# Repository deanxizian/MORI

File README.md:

# MORI：正式机器人与可行性验证小车

本仓库包含两个独立维护和编号的项目。各项目的版本、模型、硬件、软件与验证状态见对应入口；两者的实测结果不互相继承。

| 项目 | 用途 | 入口 |
|---|---|---|
| 正式机器人 | WeAct STM32F412 主控、四执行器机器人 | **[robot/](robot/README.md)** |
| 可行性验证小车 | 树莓派 4B 两轮平衡与模块验证 | **[test_rig/](test_rig/README.md)** |

## 目录结构

```text
MORI/
├── robot/          正式机器人：尺寸、合同、机械、PCB、固件、应用、文档与工具
├── test_rig/       验证小车：结构、模块、控制源码、关键实测记录
├── projects.json   两个项目的入口与版本清单位置
├── tools/          仓库级完整性检查
└── .github/        两项目独立检查工作流
```

## 资料入口

- [版本与目录规则](VERSIONING.md)
- 正式机器人：[当前需求](robot/docs/REQUIREMENTS.md) · [当前状态](robot/docs/CURRENT_STATUS.md) · [资料索引](robot/docs/PROJECT_INDEX.md)
- 验证小车：[装配说明](test_rig/ASSEMBLY.md) · [当前状态](test_rig/STATUS.md) · [控制源码](test_rig/control/README.md)
- [正式机器人下载与重建](robot/docs/GITHUB_ARCHIVE.md)

## 离线检查

Python 3.12+ 离线检查，不连接硬件：

```sh
python3 tools/check_workspace.py --allow-lfs-pointers
python3 robot/tools/check_project.py --allow-lfs-pointers
python3 test_rig/tools/check_release.py
```

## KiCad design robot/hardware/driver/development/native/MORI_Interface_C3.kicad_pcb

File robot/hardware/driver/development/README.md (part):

# C3 收尾开发工作区

当前本地开发入口为 **C3 R188C / 19 项未连接**。R188 已修复 U1702 比较器输入的局部参考地缺口，并缩短 C1002 的直接回地路径；没有再消除未连接项。原 40 项中的剩余比例仍为 47.5%，不代表工程或时间完成率。

最新 [R190 研究](evidence/R190_study/README.md)已归档，A/B/C 均未采用。B 为 19 未连接 / 0 其他 DRC，但完整接收检查未完成；C 接通 RAW 后损坏原供电和热连接，已拒绝。入口与 77 个非 PCB 源成员保持。用户已允许评估 70×40 mm 的机械空间，安装孔和接口保持；独立机械检查尚未完成，也没有采用扩板。

[R188C 接收说明](evidence/R188C/README.md) · [R188 三稿比较](evidence/R188_study/README.md) · [当前参考地待审队列](evidence/R188C/reference-review-queue.json) · [R182 空间比较](evidence/R182_study/README.md) · [继续开发](NEXT.md)

此前 [R189 四稿比较](evidence/R189_study/README.md)均未采用。R1304 在保留相邻走线的 12 个几何姿态中未找到两端完整访问；这是限定搜索，不是整板不可布通的证明。A–C 割裂 CAM 供电，A 还孤立一处地焊盘；D 恢复全部原连接和 50 项供电检查，但 J401 正面接地热焊盘仍有一条引线接入死铜，原生 DRC 不通过。下一步把 R402、相邻 WHEEL_BUS 出线、R1304 输入和 OV 换层一起重排，并保留真实供电及接地热连接。当前板框、R188C 原生文件及 77 个非 PCB 成员均保持，参考地待审队列仍为 75 段／36 网。

R188C 的 19 未连接 / 0 其他 DRC / 0 图板差异 / 0 启用 ERC、2524 项精确修改检查、50 供电铜宽、155 地焊盘单组、63 关键邻接及新旧参考地回归通过。一只地孔与一只采样孔按明确计划移动，10 段换成 13 段；C1002 的 0.20 mm 宽直接回地从 4.043503 mm 缩短至 2.568503 mm。没有移动器件、增加孔或更改板框／规则。当前 1418 段 / 324 孔 / 215 器件；114 地孔身份保留，其中 113 个位置不变，全部仍接触两参考层的实际地填铜。77 个非 PCB 成员原字节保持，十张源板／最终局部图已实际查看。

完整参考地扫描覆盖 1305 段非 GND 走线，待审项从 R187F 的 76 段／37 网降至 **75 段／36 网**；U1702 INA+ 原约 0.318712 mm² 缺口消除，未新增或恶化保留走线的缺口。这些是几何筛查提示，不是原生 DRC 或已证实电气故障。采样线对相邻 In2 接收端电源面新增约 0.001729 mm² 未屏蔽投影，按更近的连续 In4 地、原层叠与缩短的回地逐项审查，仅接受为开发布局。最近两处过孔名义铜间距约 0.204／0.208 mm，满足原规则，但没有推定额外加工裕量。六项历史换层提示、完整噪声／热／瞬态和实物资格仍未完成。

供电规划保护已按 R188C 重新计算，50 项原连接／铜宽及 50 项序列化读回检查通过，供下一轮使用。完整参考地扫描沿用 `scripts/audit_reference_coverage.py`，原阈值／自身换层豁免规则保持。[R187F](evidence/R187F/README.md)已消除的 IMU 时钟四处和 WHEEL_TX 一处缺口保持；其扫描器与冻结源板 1296 段逐段核对的历史证据不改写。

此前 R186 四稿均未采用。分压／滤波四件换位能放下局部支路，但完整端点未恢复；D 接回两条诊断路线后损失 7 项供电检查，GND 分成 153+2，已拒绝。局部拥挤明确，仍未证明整板必须扩大。[R186 源板扫描](evidence/R186_study/README.md)的 81 段／38 网属于 R181C 历史结果，当前以 R188C 队列为准。

此前 R185 也未采用 PCB 修改。独立 I 缩短 C601 回地并补回 3.3 V，2508 项数字核对通过、历史换层提示降到 5 项，但 TVS／相邻层控制线的耦合审查未关闭；J 的绕行又产生新参考地缺口。原地孔位置一律冻结是早期工具限制，已更正为明确计划下的地孔移动及直接回地校验；R186 又补齐真实焊盘内部偏移出口的六项正反例。原生规则和验收要求保持。

地孔参考连接检查也已改用实际填铜，排除自身铜环造成的假阳性；五项正反例及 I 的 2508 项重跑通过，当前板与候选的既有计数均未改变，旧证据保留。

此前 R184 未采用任何修改。扩大到门极 RC 后，充电泵电容的移位仍受原 UPS 5 V 供电桥限制；独立释放桥线才出现新的几何组合。原生 D 虽能放下器件，仍为 26 未连接 / 3 悬空过孔，供电只过 46/50，未接收；下一步须把实际换层孔与完整供电恢复纳入同一布局。有限搜索不证明整板不可布通。[R182](evidence/R182_study/README.md)已准备 **70×40 mm 独立空间候选**及静态比较：只沿原生 +Y 加 5 mm，孔/接口不动；候选尚未布通、没有新增区域参考地或机械适配，不能制造。用户已允许评估其机械空间；评估尚未完成，尚未采用。当前板仍为 70×35 mm / R188C / 19 项未连接。

[此前 R181 比较](evidence/R181_study/README.md)保留 A–H，仅接收 C 的采样支路。其余联合移动、供电冲突或参考地失败方案均未采用；R182 按新源重新生成供电保护，没有沿用旧源检查冒充通过。

R181C 曾将采样支路从 25.512702 mm 缩短到 18.203088 mm，改走 F.Cu 并复用两处原换层孔，退休一个无剩余连接的非地孔。该阶段 2523 项精确差异及电气回归通过，为 1409 段 / 324 孔 / 215 器件，八张局部/源板图已查看。该支路距 Q1602 漏极焊盘最小名义铜间距 0.2225 mm，距 C707.1 为 0.375 mm；这些数值和 DRC 不能证明采样噪声、瞬态或热性能合格。源证据完整保留。

本目录是从 `main aa94ddd` / C3 R108P 原包恢复的**独立开发候选**，尚未采用到当前发布，也没有制造或实物资格。正式已发布入口仍为上级 R108P。

任务：完成接口板剩余连线及规范审查。保留 70 × 35 × 1.6 mm 六层板、四安装孔、68 核心针位、九连接器、既定电路和保护策略。优先向器件外侧出线，比较朝向/位置，避免多余绕折；电源/去耦关键环路优先。确有必要的例外须逐项说明。

验收包含：

1. 原生填铜后的全严重级 DRC、未连接、图板一致性和 ERC；明确历史忽略项，不降低规则。
2. 全部旧连接组、供电铜宽、GND、Kelvin 取样、关键器件邻接和敏感区回归。
3. 连续参考地及历史换参考层提示（原七项，R129D 后剩六项）；新增孔不可割裂供电，也不可破坏旧信号参考地。
4. 全板逐线/逐孔与各层静态视觉审查；自动几何筛查不代替实际看图。
5. 电源/保护/连接器额定及完整 BOM、接口针表、机械交接、线束和采购成本。缺实测/厂家数据须明确保留，不能凭连通或 DRC 放行。
6. 可复查的原生工程、来源和修改清单、实际命令与输出、复现脚本；通过 PR 发布，合并须针对该 PR 授权。

不运行设备、不烧录、不下单、不在未布完时导出制造文件。旧发布 ZIP、原始厂家资料和冻结证据不被覆盖。物理热/浪涌/EMC/动态性能保持 NOT_TESTED，直到有相应实测证据。

## 发布快照与复现

[本次发布审查与原生复查](evidence/publication_20261029/README.md)保留固定接口、原连接、归档完整性、离线测试及明确未完成项。

本次 PR 以一个汇总提交发布当前入口与冻结研究资料。历史记录中的中间提交号只标识本地来源，不要求这些提交出现在远端历史中。复现以文件哈希为准：当前 `native/` 的 77 个非 PCB 成员与 R108P 原包保持原字节，旧版源 PCB 在各接收/研究目录中保留；恢复对应源 PCB、计划和依赖后，在独立目录运行开发脚本。历史命令及冻结脚本中的本机路径、源 HEAD 断言记录当时环境，不能把它们当成新机器可直接运行的配置，也不要改写冻结记录以制造一致。

## 本机复现环境

KiCad 10.0.7；其自带 Python 3.9.13 用于原生 `pcbnew`，独立环境在 `robot/.state/c3-completion/venv`，几何计算用 Shapely 2.0.7。仓库完整性脚本另用 Python 3.12+。`.state` 中的基线由上级 ZIP 解出，78 个成员均按 manifest 验证。

本机原生基线复查：40 项未连接，其他 DRC 0，图板差异 0；启用项全严重级 ERC 0。没有据此提高工程资格。

## 已保留的 R178L 接收记录

以下为对应修订的历史记录；当前入口以本文开头和 STATUS.json 为准。

2026-10-29，D302 改为正面 `(2,23)` / 270°，保留原型号、极性及原生禁布区，以两条短线接到已有 CLR/FAULT 过孔。当前 **19 项未连接，0 其他 DRC / 图板差异 / 启用 ERC**；剩余数量比例 **47.5%**，不是工程或时间完成率。

2515 项精确修改核对、全部原连接、50 铜宽、155 地焊盘、63 邻接及新旧参考地通过；114 原地孔、全部其他原孔、固定接口和 77 个非 PCB 成员保持。九张局部图已查看，新 FAULT 避开对侧 DVDT 铜及电感本体投影；全板、厂家完整布局及实物资格仍未完成。正式发布仍为 R108P，不可制造。

[当前接收记录](evidence/R178L/README.md) · [原生结果](evidence/R178L/result.json) · [精确核对](evidence/R178L/planned-delta.json) · [剩余连接](evidence/R178L/remaining_connections.csv) · [对比研究](evidence/R178_study/README.md) · [继续开发](NEXT.md)

## 前一已采用开发稿：C3 R168G

2026-10-28，Q1701 的 FAULT 支路已接入主组，现为 **20 项未连接，0 其他 DRC / 图板差异 / 启用 ERC**。FAULT 尚余 U1701.5、D302.1 两个孤立端。**20/40 = 50% 仅为剩余未连接数量比例**，不是工程或时间完成率。

联合调整 Q1701、U1702、C1702 和三只原非地过孔，完整恢复原引线，新增一只 FAULT 孔及 21.090180 mm In2 主干。2566 项明确差异、全部旧连接、50 铜宽、155 地焊盘、63 邻接及新旧参考地通过；114 原地孔、原 0.48 mm 供电通道、固定接口和 77 个非 PCB 源成员保留。现为 1398 段 / 325 孔 / 215 器件。

十二张局部六层图已实际检查，无新同面名义本体穿越。对侧/内层投影和四处跨层交叉已记录边界；完整输入噪声、去耦环路、保护动态、热/耦合与实物仍未资格化。正式已发布入口仍为 R108P，不可制造。

[接收说明](evidence/R168G/README.md) · [检查结果](evidence/R168G/result.json) · [精确差异](evidence/R168G/planned-delta.json) · [局部审查](evidence/R168G/visual_review.json) · [剩余连接](evidence/R168G/remaining_connections.csv) · [未采用研究](evidence/R168_study/README.md)

后续 [R169 研究](evidence/R169_study/README.md)比较 INA300 原朝向与 180° 朝向，并联合调整 R1310。E 接通 FAULT 支路，却割裂 3.3 V，且原取样、LIMIT 与显式回地未恢复，未采用。原生入口及 **20 项 / 50%** 不变；具体下一步见 [继续开发](NEXT.md)。

[R170 研究](evidence/R170_study/README.md)继续比较原出口与四只无源器件成组调整，保留十块原生稿。J 已恢复 IN− 短线及部分原供电，但 3.3 V 孔／引线禁布冲突、旧连接和 RLIMIT 显式回地仍未完成，未采用；当前入口与 **20 项 / 50%** 不变。

[R171 研究](evidence/R171_study/README.md)显式核对旧 VS 孔的孤立内层铜区，并在 E 恢复 VS 与 ENABLE。E 为 27 项未连接、5 项悬空，旧连接及 RLIMIT 显式回地仍未完成，未采用。已采用 R168G 与 **20 项 / 50%** 保持；原生失败、工具正反例及五张局部图均保留。

[R172 空间检查](evidence/R172_study/README.md)确认 INA300 附近局部拥挤，但尚未证明整板面积不足。依赖筛查指出需扩大到 U1302 等相关器件联合排布；未构建新板，入口与 **20 项 / 50%** 不变。具体空间限制须及时报告，板框或已确认结构变化先以模型和静态对比确认。

[R173 联合布局研究](evidence/R173_study/README.md)构建四块比较稿；E 有显式 RLIMIT 回地，但五项实际 3 mm 邻接要求、原供电／连接和一处新参考地缺失仍失败，全部未采用。下一步联合安排两颗 IC 和全部六只外围；当前入口及 **20 项 / 50%** 不变。

[R174 完整布局与供电对照](evidence/R174_study/README.md)的六块原生稿均满足 63 项邻接要求，但仍未采用。D 有显式 RLIMIT／去耦回地；单项撤销对照分别确认新 IN− 孔削弱 UPS 0.48 mm 通道、In3 回地割裂 3.3 V 宽铜通道。局部空间瓶颈已报告，尚未证明必须扩板；原连接和供电须一起恢复。采用入口及 **20 项 / 50%** 不变。

[R175 供电保护与端口研究](evidence/R175_study/README.md)保留九块原生候选。A 恢复上述 UPS／3.3 V 宽铜回归；G 通过监控器／电容旋转恢复 155 个地焊盘单组并构建较短的显式回地。A／G 均为 31 opens / 7 dangling / 0 parity / 0 enabled ERC，原连接与供电支路仍未恢复，全部未采用。正输入、CT 及其他支路继续成组布局／出线检查，扩大板框的必要性仍未证明；当前入口及 **20 项 / 50%** 不变。

[R176 原针位与供电研究](evidence/R176_study/README.md)保留 11 块原生候选。H 恢复两路输入、LIMIT 和 155 地焊盘单组，但 25.593 mm 新回地割裂了 3.3 V 分配；后续短接和 In2 修复也出现其他供电或参考地退化，全部未采用。已记录 C1601／INA300 周边的明确装配包络冲突；局部拥挤有证据，必须扩板尚未证明。禁布分区工具修复通过 18 项检查及四次原生重读，原生规则未放宽。当前入口仍为 **R168G / 20 项 / 50% 连通数量比例**。

[R177 供电保护与 D302 比较](evidence/R177_study/README.md)建立了覆盖全部 50 项原供电检查、读回验证通过的规划保护，并保存 11 块原生稿。G 达到 19 / 0 / 0 / 0，但新增 CLR 的 L701／SW 投影审查尚未闭合；K 避开 L701，却违反 J102.2 的四条热连接要求。两稿均未采用，当前仍 **20 项 / 50%**。局部空间限制有证据，尚未证明必须扩板；不能把候选连通或数字检查通过写成工程完成。

## 先前接收：C3 R165M

以下是当时的接收与后续研究记录；当前入口以上方 R168G 为准。

2026-10-28，原生开发入口为 **R165M，21 项未连接，0 其他 DRC / 图板差异 / 启用 ERC**。U1301 的 OV 网络由两组接成一组；联合布局中涉及的原 UV、FAULT 和 ENABLE 偏置连接全部恢复。原理图、值、针表、固定接口和规则保持。

17 个器件成组调整，其中两只电阻换面；以显式计划替换旧铜和非地换层孔，全部 114 个原地孔保留。原 OV 孔移至 `(55.9,33.9)`，FAULT 接入孔位于 `(54.3,33.9)`，让两条输出信号通过既有 3.3 V 孔之间的有参考地通道。现为 1366 段 / 324 孔 / 215 器件。

2807 项计划差异、全部旧连接、50 项铜宽、155 地焊盘、63 邻接及新旧参考地检查通过。十二张原生几何图已实际审查，新同面名义本体穿越为 0；16 组对侧/内层器件投影明确记录参考地、耦合和热检查边界。77 个非 PCB 工程成员保持原字节。

**21/40 = 52.5% 仅为剩余未连接数量比例。** 六项历史回流提示、整板风格、完整厂家布局、热/耦合和实物资格未完成；正式发布仍 R108P，机械与软件未采用，不可制造。

[接收说明](evidence/R165M/README.md) · [当前结果](STATUS.json) · [剩余连接](evidence/R165M/remaining_connections.csv) · [图审](evidence/R165M/visual_review.json) · [R165 研究](evidence/R165_study/README.md) · [继续开发](NEXT.md)

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
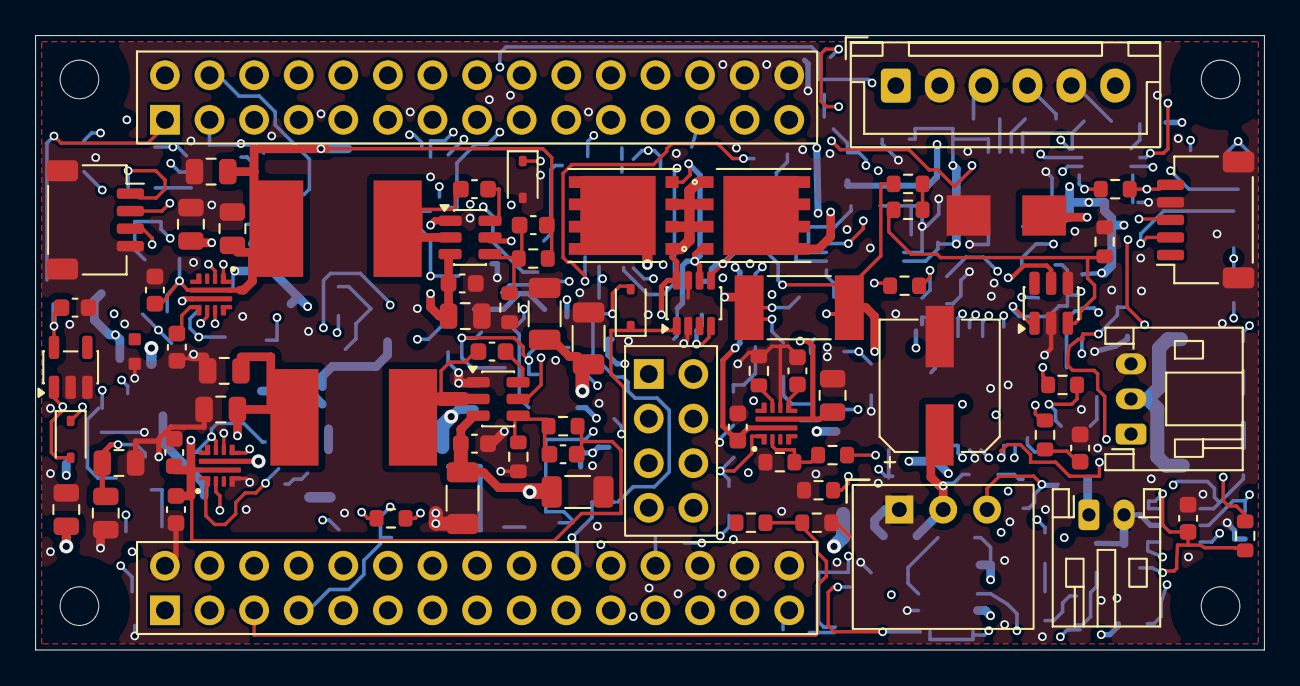
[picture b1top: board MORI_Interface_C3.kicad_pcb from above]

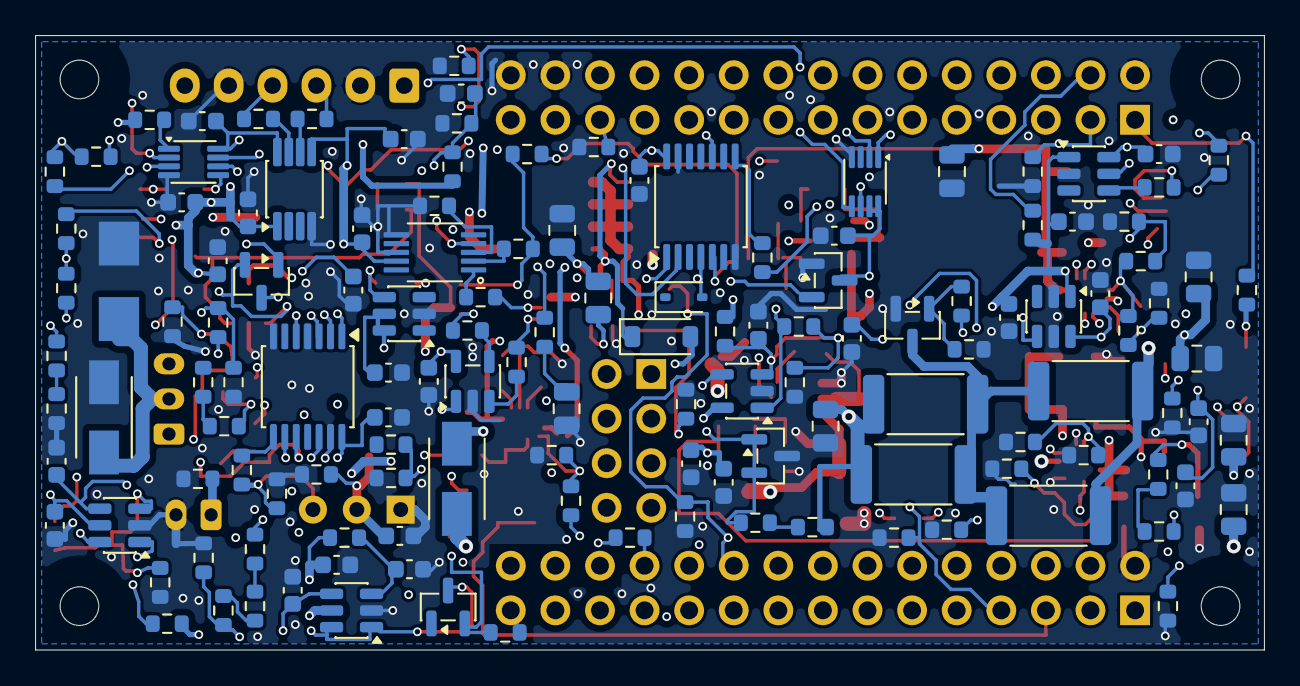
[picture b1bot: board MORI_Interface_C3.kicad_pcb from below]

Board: 6 copper layers, 70.0 x 35.0 mm, 215 parts (135 on the bottom side), 106 nets.

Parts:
C301, C302, C303, C401, C402, C501, C502, C503, C504, C601, C602, C702, C706, C906, C1001, C1002, C1003, C1101, C1102, C1202, C1209, C1303, C1304, C1402, C1502, C1503, C1701, C1702: 100nF 16V X7R; C_0603_1608Metric
C505, C708, C803, C1201, C1401: 1uF 16V X7R; C_0603_1608Metric
C701, C703, C704, C705, C709, C802, C903, C904, C905, C909, C910, C911, C1205, C1206, C1207, C1208: 22uF 25V X5R; C_0805_2012Metric
C707, C907, C1301, C1302, C1403, C1501: 100pF 50V C0G; C_0603_1608Metric
C710, C801, C1203, C1204: 1nF 50V C0G; C_0603_1608Metric
C901, C908, C912, C913: 10uF 50V X7R; C_1206_3216Metric
C902: 100nF 50V X7R; C_0603_1608Metric
C1404: 220uF 16V polymer; Panasonic_SVPF_C6
C1601, C1602, C1603: 220nF 50V X7R; C_0805_2012Metric
D301, D302, D1001, D1601: BAT54WS-7-F; D_SOD-323
D901, D1803: B340LA-13-F; Diodes_SMA
D1602: BZT52C12-7-F; D_SOD-123
D1801, D1802: SMBJ13CA-13-F; Diodes_SMB
H1, H2, H3, H4: MountingHole_2.2mm_M2
J101, J102: X6521FV-2x15-C85D32; XKB_2x15_WeAct_AC_BD_ConnectedInner6L
J105: PM254-2-04-Z-8.5; HCTL_2x04_WeAct_E_ConnectedInner6L
J401: S3B-PH-K-S(LF)(SN); JST_PH_S3B-PH-K_1x03_P2.00mm_Horizontal_ConnectedInner6L
J402: HC-5264-3AW; HCTL_5264_3AW_ConnectedInner6L
J501: SM04B-SRSS-TB(LF)(SN); JST_SH_SM04B-SRSS-TB_1x04-1MP_P1.00mm_Horizontal
J502: SM05B-SRSS-TB(LF)(SN); JST_SH_SM05B-SRSS-TB_1x05-1MP_P1.00mm_Horizontal
J701: B6B-XH-A(LF)(SN); JST_XH_B6B-XH-A_1x06_P2.50mm_Vertical_ConnectedInner6L
J702: S2B-PH-K-S(LF)(SN); JST_PH_S2B-PH-K_1x02_P2.00mm_Horizontal_ConnectedInner6L
L701: 10uH MWSA0804S-100MT; L_Sunlord_MWSA0804S
L901: 10uH; L_Sunlord_MWSA0804S
Q1301, Q1401, Q1701: AO3400A; SOT-23
Q1601, Q1602: CSD17577Q5A; TI_CSD17577_Q5A
R301, R305, R403, R406, R716, R802, R804, R1207, R1704: 10k; R_0603_1608Metric
R302, R303, R304, R404, R407, R903, R1031, R1032, R1033, R1201, R1301, R1310, R1311, R1312, R1407, R1602, R1702, R1703, R1705: 100k; R_0603_1608Metric
R402, R405, R501, R502, R603, R604, R1406: 33R; R_0603_1608Metric
R505, R506, R601, R602, R1309: 4.7k; R_0603_1608Metric
R701, R1001, R1002, R1305, R1502: 54.9k 0.1%; R_0603_1608Metric
R702, R712, R714, R902, R1011, R1012, R1205, R1303, R1306, R1307, R1404, R1504: 10k 0.1%; R_0603_1608Metric
R711, R1302, R1505: 18k; R_0603_1608Metric
R713, R1202, R1203, R1503: 24.3k 0.1%; R_0603_1608Metric
R715, R1206: 1.65k; R_0603_1608Metric
R801: 27k; R_0603_1608Metric
R803: 36k; R_0603_1608Metric
R805: 3.32k; R_0603_1608Metric
R806, R1003, R1021, R1022, R1102, R1208, R1401, R1402, R1601: 1k; R_0603_1608Metric
R901, R1304, R1501: 90.9k 0.1%; R_0603_1608Metric
R1101: 20mR 1% 1W; Vishay_WSL2512_20mR
R1103, R1104, R1706, R1707: 220R; R_0603_1608Metric
R1308: 100k; R_0603_1608Metric_R1308Edge
R1403: 16.5k 0.1%; R_0603_1608Metric
R1405: 1M; R_0603_1608Metric
R1411, R1412, R1413, R1414: 10R / 2W pulse; R_2512_6332Metric
R1701: 1.74k; R_0603_1608Metric
TH1501: 10k NTC / 3435K; TDK_NTCG_1608
U301: SN74LVC1G74DCUR; VSSOP-8_2.3x2mm_P0.5mm
U302: STWD100NXWY3F; SOT-23-5
U303: TLV803EA29DBZR; SOT-23
U401: SN74LVC2G32DCUR; VSSOP-8_2.3x2mm_P0.5mm
U402: 74LVC125APW,118; TSSOP-14_4.4x5mm_P0.65mm
U501, U502: SN74LVC1T45DBVR; SOT-23-6
U601: TCA9517DGKR; VSSOP-8_3x3mm_P0.65mm
U701, U901: TPS54302DDCR; SOT-23-6
U702, U801: TPS259470LRPWR; TI_RPW0010A
U1001: TMUX1511PWR; TSSOP-14_4.4x5mm_P0.65mm
U1101: INA180A2IDBVR; SOT-23-5
U1201: TPS259474LRPWR; TI_RPW0010A
U1301, U1501, U1702: TPS3700DDCR; SOT-23-6
U1302: TPS3808G01DBVR; SOT-23-6
U1401: TLV1811DBVR; SOT-23-5
U1402: TL431BIDBZR; SOT-23
U1601: LM74502DDFR; Texas_DDF0008A_SOT-8_1.6x2.9mm_P0.65mm
U1701: INA300AIDGSR; TI_DGS0010A

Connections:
/01 / Core/ACT_CURRENT_ADC: J101.7, R1003.2, R1033.2
/01 / Core/ARMED: D1601.2, J101.20, R304.1, R903.2, R1201.2, U301.3, U901.5, U1201.1, U1302.3
/01 / Core/ARM_CLK: J102.3, R302.1, U301.1
/01 / Core/BAT_ADC: J101.5, R1021.2, R1031.1
/01 / Core/HEAD_OE_REQ_N: J102.6, R406.2, U401.5
/01 / Core/HEAD_RX: J101.14, U402.11
/01 / Core/HEAD_TX: J101.11, U402.9
/01 / Core/IMU_SCL: J102.17, J502.3, R506.2
/01 / Core/IMU_SDA: J102.20, J502.2, R505.2
/01 / Core/LINK_RX: J102.22, U502.3
/01 / Core/LINK_TX: J102.21, U501.3
/01 / Core/MOTION_5V: C802.1, J102.27, J102.29, U801.6
/01 / Core/NRST: D301.1, J105.7
/01 / Core/UPS_SCL_MCU: J101.24, R601.2, U601.2
/01 / Core/UPS_SDA_MCU: J102.1, R602.2, U601.3
/01 / Core/WDI: J102.25, R303.1, U302.4
/01 / Core/WHEEL_ADC: J101.8, R1022.2, R1032.2
/01 / Core/WHEEL_OE_REQ_N: J102.5, R403.2, U401.1
/01 / Core/WHEEL_RX: J102.15, U402.6
/01 / Core/WHEEL_TX: J102.18, U402.2
/03 / Motor_Buses/DISARMED: U301.5, U401.2, U401.6
/03 / Motor_Buses/HEAD_BUS: J402.3, R405.2, R407.1, U402.12
/03 / Motor_Buses/WHEEL_BUS: J401.1, R402.2, R404.1, U402.5
/06 / CAM_Buck/CAM_REG_3V87: C703.1, C704.1, C705.1, C707.1, C708.1, L701.2, R701.2, R711.2, R713.2, U702.5
/06 / CAM_Buck/UPS_5V: C701.1, C702.1, C803.1, J701.1, R801.2, R803.2, R806.2, U701.3, U701.5, U801.5
/07 / CAM_Protection_Start/CAM_BAT_OUT: C709.1, J702.1, R716.2, U702.6
/09 / Head_Buck/HEAD_BUCK_IN: C901.1, C902.1, C908.1, C912.1, C913.1, D901.1, U901.3
/13 / Head_Fault_Delay/HEAD_UV_N: Q1301.2, R1308.1, U1301.1
/14 / Head_Regen/HEAD_REF_2V495: R1402.1, U1401.4, U1402.1, U1402.2
/14 / Head_Regen/H_DUMP_SENSE: C1403.1, R1403.1, R1404.2, R1405.1, U1401.3
/15 / Head_Output_OV/H_DUMP_TEMP: C1503.1, R1505.1, TH1501.1, U1501.3
/16 / Actuator_Direct_Switch/ACT_FET_SOURCE: D1602.2, Q1601.1, Q1601.2, Q1601.3, Q1602.1, Q1602.2, Q1602.3, U1601.8
/16 / Actuator_Direct_Switch/ACT_GATE: D1602.1, Q1601.4, Q1602.4, R1601.1, U1601.6
/17 / Actuator_Overcurrent/ACT_UV_N: Q1701.2, R1705.1, U1702.1
/ACT_BAT_SWITCHED: Q1602.5, Q1602.6, Q1602.7, Q1602.8, R1101.1, R1103.1, R1706.1
/ACT_CURRENT_FILTERED: C1102.1, R1102.2, U1001.9
/CLR_N: D301.2, D302.2, J102.4, R301.1, U301.6, U302.1, U303.2, U1001.1, U1001.4, U1001.10
/FAULT_N: D302.1, J102.7, Q1301.3, Q1701.3, R305.2, U1301.6, U1501.1, U1501.6, U1701.5
/HEAD_6V_RAW: C903.1, C904.1, C905.1, C907.1, C909.1, C910.1, C911.1, C1201.1, C1202.1, L901.2, R901.2, R1202.2, R1304.2, U1201.5
/HEAD_UV_ENABLE: Q1301.1, Q1701.1, R1309.1, R1311.2, U1302.1
/HEAD_VM: C1205.1, C1206.1, C1207.1, C1208.1, C1209.1, C1401.1, C1402.1, C1404.1, J402.2, R1208.2, R1301.2, R1401.2, R1403.2, R1411.2, R1412.2, R1413.2, R1414.2, R1501.2, U1201.6, U1401.5
/UPS_BAT: C1601.1, C1602.2, D1801.1, J701.6, Q1601.5, Q1601.6, Q1601.7, Q1601.8, R1001.1, U1601.5
/WHEEL_VM: D901.2, D1802.1, D1803.1, J401.2, R1002.1, R1101.2, R1104.1, R1702.1, R1707.1
CAM_3V3_REF: C502.1, C504.1, J501.3, U501.6, U502.6
GND: C301.2, C302.2, C303.2, C401.2, C402.2, C501.2, C502.2, C503.2, C504.2, C505.2, C601.2, C602.2, C701.2, C702.2, C703.2, C704.2, C705.2, C708.2, C709.2, C710.2, C801.2, C802.2, C803.2, C901.2, C902.2, C903.2, C904.2, C905.2, C908.2, C909.2, C910.2, C911.2, C912.2, C913.2, C1001.1, C1002.2, C1003.2, C1101.2, C1102.2, C1201.2, C1202.2, C1203.2, C1204.2, C1205.2, C1206.2, C1207.2, C1208.2, C1209.2, C1301.2, C1302.2, C1303.2, C1304.2, C1401.2, C1402.2, C1403.2, C1404.2, C1501.2, C1502.2, C1503.2, C1601.2, C1603.2, C1701.2, C1702.2, D1001.2, D1801.2, D1802.2, D1803.2, J101.2, J101.26, J101.28, J101.30, J102.2, J102.28, J102.30, J401.3, J402.1, J501.4, J501.MP, J502.4, J502.MP, J701.2, J701.5, J702.2, Q1401.2, R302.2, R303.2, R304.2, R404.2, R407.2, R702.1, R712.1, R714.1, R715.1, R716.1, R802.1, R804.1, R805.1, R806.1, R902.1, R903.1, R1011.2, R1012.1, R1031.2, R1032.1, R1033.1, R1201.1, R1205.1, R1206.1, R1207.1, R1208.1, R1303.1, R1307.1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
MOTION_3V3: C301.1, C302.1, C303.1, C401.1, C402.1, C501.1, C503.1, C505.1, C601.1, C602.1, C1003.1, C1101.1, C1303.1, C1304.1, C1502.1, C1701.1, C1702.1, J101.25, J101.27, J101.29, J502.5, R301.2, R305.1, R403.1, R406.1, R505.1, R506.1, R601.1, R602.1, R1308.2, R1309.2, R1310.2, R1505.2, R1705.2, U301.2, U301.7, U301.8, U302.5, U303.3, U401.8, U402.14, U501.1, U501.5, U502.1, U601.1, U601.5, U601.8, U1001.14, U1101.5, U1301.5, U1302.5, U1302.6, U1501.5, U1701.4, U1701.9, U1702.5
unnamed: C1603.1, R1601.2
unnamed: C1001.2, D1001.1, R1001.2, R1011.1, U1001.2
unnamed: D1601.1, R1602.2, U1601.1
unnamed: J501.1, R501.2
unnamed: J501.2, R502.2
unnamed: J701.4, R603.2
unnamed: J701.3, R604.2
unnamed: Q1401.3, R1411.1, R1412.1, R1413.1, R1414.1
unnamed: Q1401.1, R1406.2, R1407.2
unnamed: R1202.1, R1203.2
unnamed: R1301.1, R1302.2
unnamed: R1304.1, R1305.2
unnamed: R1305.1, R1306.2
unnamed: R1311.1, R1312.2
unnamed: R1401.1, R1402.2
unnamed: R1501.1, R1502.2
unnamed: R1502.1, R1503.2
unnamed: R1702.2, R1703.1
unnamed: U401.7, U402.1
unnamed: U401.3, U402.10
unnamed: R402.1, U402.3
unnamed: R405.1, U402.8
unnamed: R501.1, U501.4
unnamed: R502.1, U502.4
unnamed: R603.1, U601.7
unnamed: R604.1, U601.6
unnamed: C706.1, U701.6
unnamed: C707.2, R701.1, R702.2, U701.4
unnamed: C706.2, L701.1, U701.2
unnamed: C710.1, U702.7
unnamed: R711.1, R712.2, U702.1
unnamed: R715.2, U702.9
unnamed: R713.1, R714.2, U702.2
unnamed: C801.1, U801.7
unnamed: R801.1, R802.2, U801.1
unnamed: R805.2, U801.9
unnamed: R803.1, R804.2, U801.2
unnamed: C906.1, U901.6
unnamed: C907.2, R901.1, R902.2, U901.4
unnamed: C906.2, L901.1, U901.2
unnamed: R1021.1, U1001.3
unnamed: R1022.1, U1001.6
unnamed: R1003.1, U1001.8
unnamed: C1002.1, R1002.2, R1012.2, U1001.5
unnamed: R1103.2, U1101.3
unnamed: R1104.2, U1101.4
unnamed: R1102.1, U1101.1
unnamed: C1203.1, C1204.1, U1201.7
unnamed: R1206.2, R1207.2, U1201.9
unnamed: R1203.1, R1205.2, U1201.2
unnamed: C1301.1, R1302.1, R1303.2, U1301.3
unnamed: C1302.1, R1306.1, R1307.2, U1301.4
unnamed: R1310.1, U1302.4
unnamed: R1405.2, R1406.1, U1401.1
unnamed: C1501.1, R1503.1, R1504.2, U1501.4
unnamed: C1602.1, U1601.4
unnamed: R1706.2, U1701.1
unnamed: R1707.2, U1701.2
unnamed: R1701.2, U1701.3
unnamed: R1703.2, R1704.2, U1702.3

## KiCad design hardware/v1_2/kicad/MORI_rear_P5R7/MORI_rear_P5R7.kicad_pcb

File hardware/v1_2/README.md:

# MORI V1.2 硬件工程 · P5R7 契约

**2026-10-01 插合增补：**原厂 STEP 自带 E 弯针也与模型孔边相交。实物孔规格未知，61300821121 与 WeAct 的兼容性为 **BLOCKED**；[证据与厂家确认清单](reviews/weact_E_J3_20260930/E_pin_hole_addendum_20261001/README.md)。P5R7 原生工程未改。

当前运动板、后接口板为 **P5R7**；电源板为 **P5R6**，IMU 为 **P5R4**。状态为 PROTOTYPE / 实物 NOT_TESTED。P5R7 修正 WeAct E 插合与后板 J3，电路功能及 GPIO 分配保持。

[本次修改与检查](reviews/weact_E_J3_20260930/README.md) · [当前端口和接线 CSV](wiring_P5R7/README.md) · [正式机械交接](handoff/mechanical_P5R7.json) · [发布校核](reviews/weact_E_J3_20260930/publication_audit.json)

| 当前原生工程 | 尺寸 / 铜层数 | P5R7 范围 |
|---|---|---|
| [运动 P5R7](kicad/MORI_motion_P5R7/MORI_motion_P5R7.kicad_pro) | 70×35×1.6 mm / 4 | 元件面朝上、排针向下；E 八孔 X+2.54 mm；R19/R9 移位及相关线路重布 |
| [电源 P5R6](kicad/MORI_power_P5R6/MORI_power_P5R6.kicad_pro) | 80×55×1.6 mm / 4 | 保留原生工程 |
| [IMU P5R4](kicad/MORI_imu_P5R4/MORI_imu_P5R4.kicad_pro) | 20×16×1.6 mm / 2 | 保留原生工程 |
| [后接口 P5R7](kicad/MORI_rear_P5R7/MORI_rear_P5R7.kicad_pro) | 24×25×1.6 mm / 2 | J3 移至 B 面、180°、孔排 Y+1.70 mm；局部重布 |

两块 P5R7 的 KiCad 10.0.6 原生 ERC、DRC、未连接和原理图一致性问题均为 0，忽略项为空；器件本体投影及新增走线样式另有检查。运动板没有内层信号线。电源与 IMU 未修改，本次沿用其历史检查证据，未声称重新验证电气或实机性能。

WeAct 按用户确认的正确朝向交接，A–D 编号及连接保持，E7 接 NRST，其余 E 孔在载板为 NC。排母和 E 直针已有厂家目录候选，但报价、实物插深、保持力与完整堆叠未验证。核心板的新 Z 坐标有意留空，机械须复核上方元件、USB、维护访问、排母焊尾和插拔空间。

后板 J3 从顶视图看左到右为 4、3、2、1，按针号接线。对冻结机械候选的名义插座/插头/拔出路径筛查通过；当前完整装配和真实线束弯折仍待验证。旧 P5R6 不可仅翻焊插座就视为新版。

[当前连接器坐标](reviews/weact_E_J3_20260930/connector_pinmap_P5R7.csv) · [版本化 pinmap](interfaces/pinmap_V1.2-H0.5-P5R7.csv) · [版本化线束](interfaces/harness_V1.2-H0.5-P5R7.csv) · [主 BOM](bom.csv)

外部 PD/3S 充电模块尚未选定，RAW 检测源端保护仍 BLOCKED；整机已取消外露 SW1，原生开关电路与物理断电/急停实施仍需另行闭合。本次未完成该功能调整。热、纹波、动态负载、EMC、充电及实物装配均未验证。没有采购、制造订单或制造文件输出。

历史入口：[P5R6 图层与布局](layout_P5R6/index.html) · [P5R6 接线工作簿](wiring_P5R6/README.md) · [P5R6／线宽复审](reviews/P5R6_and_width_external_20260925/README.md) · [原 P5R6 四板工程包](MORI_FourBoards_P5R6_Reviewed_Projects.zip) · [板级测试计划](layout_P5R6/test_plan.md)。这些历史文件保留原版本；不作为 P5R7 的装配朝向依据。

既有未决项仍保留：电源板两条 In1 安静地对源 R13 的偏离、后板 CC2 严格倒角 FAIL 和 IMU 原短引出例外。零 DRC 不代表所有布线偏好、工艺或电气性能通过。原生板为布局真值，历史编辑脚本不得覆盖当前工程。

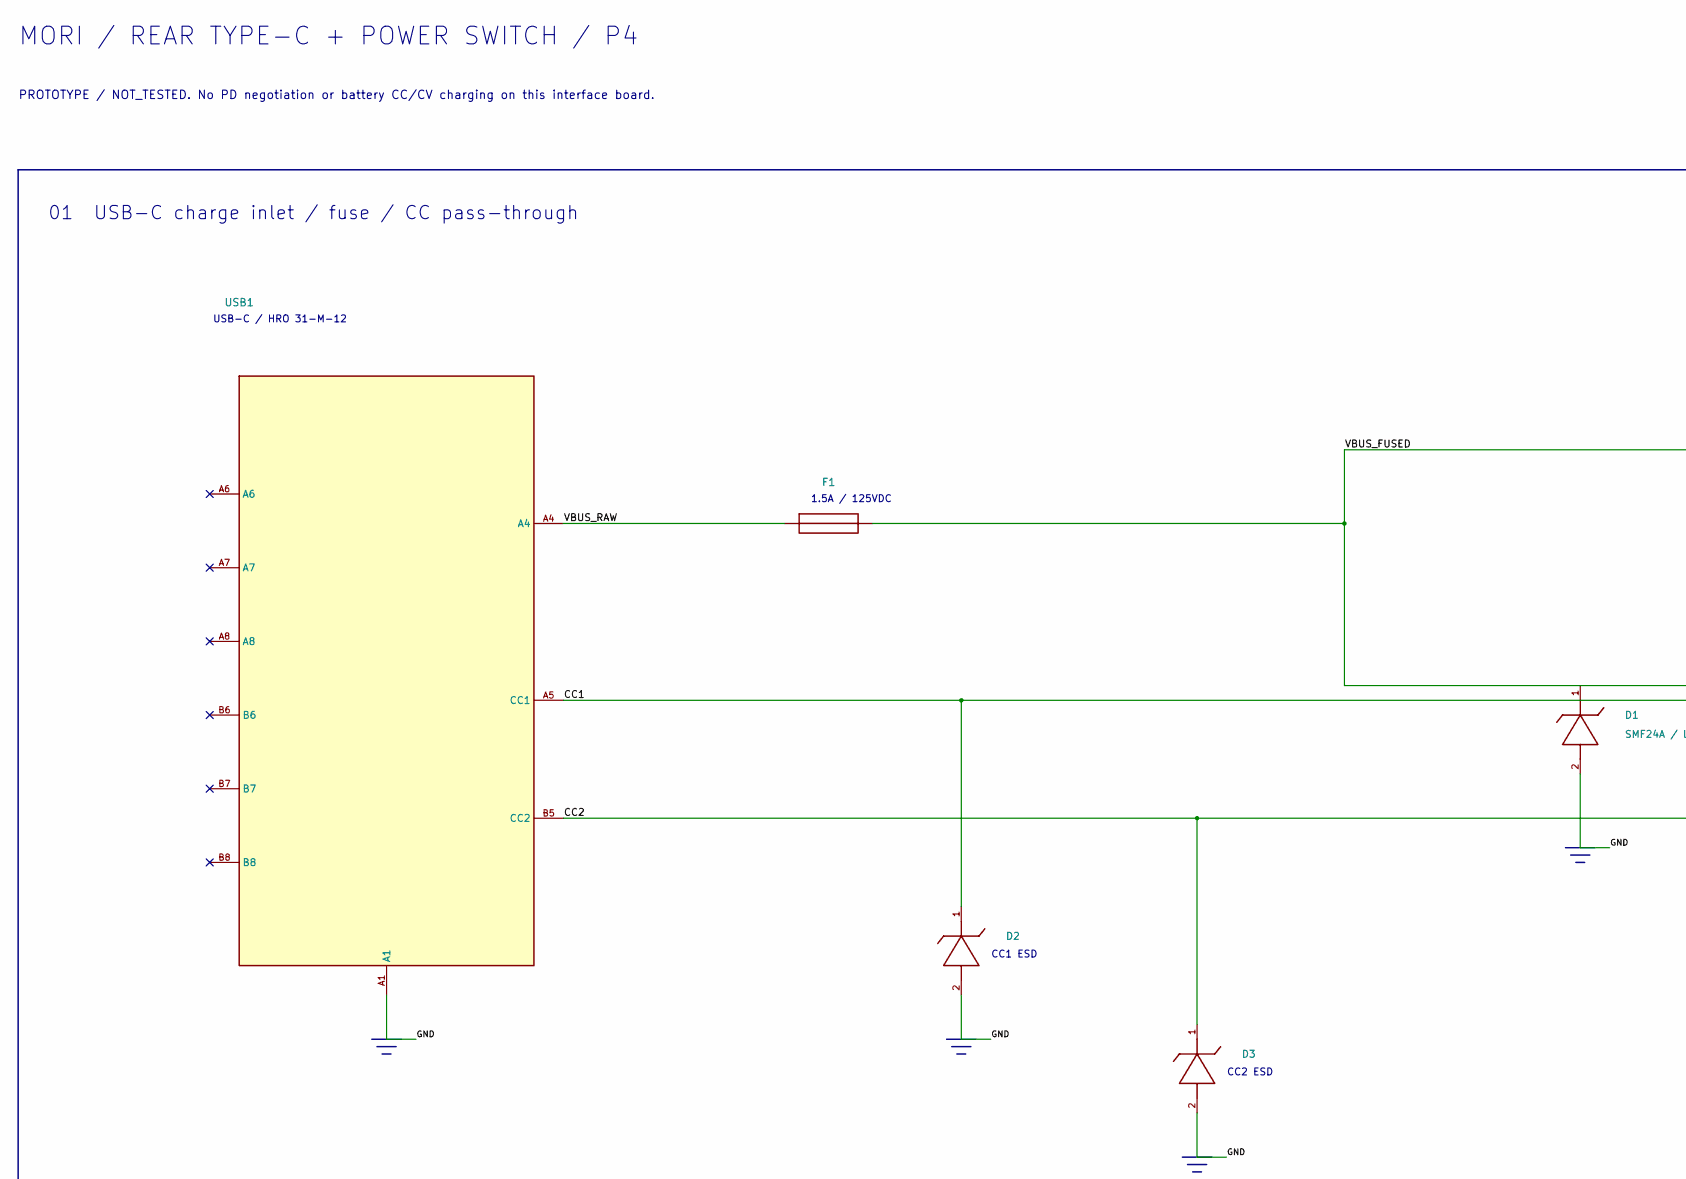
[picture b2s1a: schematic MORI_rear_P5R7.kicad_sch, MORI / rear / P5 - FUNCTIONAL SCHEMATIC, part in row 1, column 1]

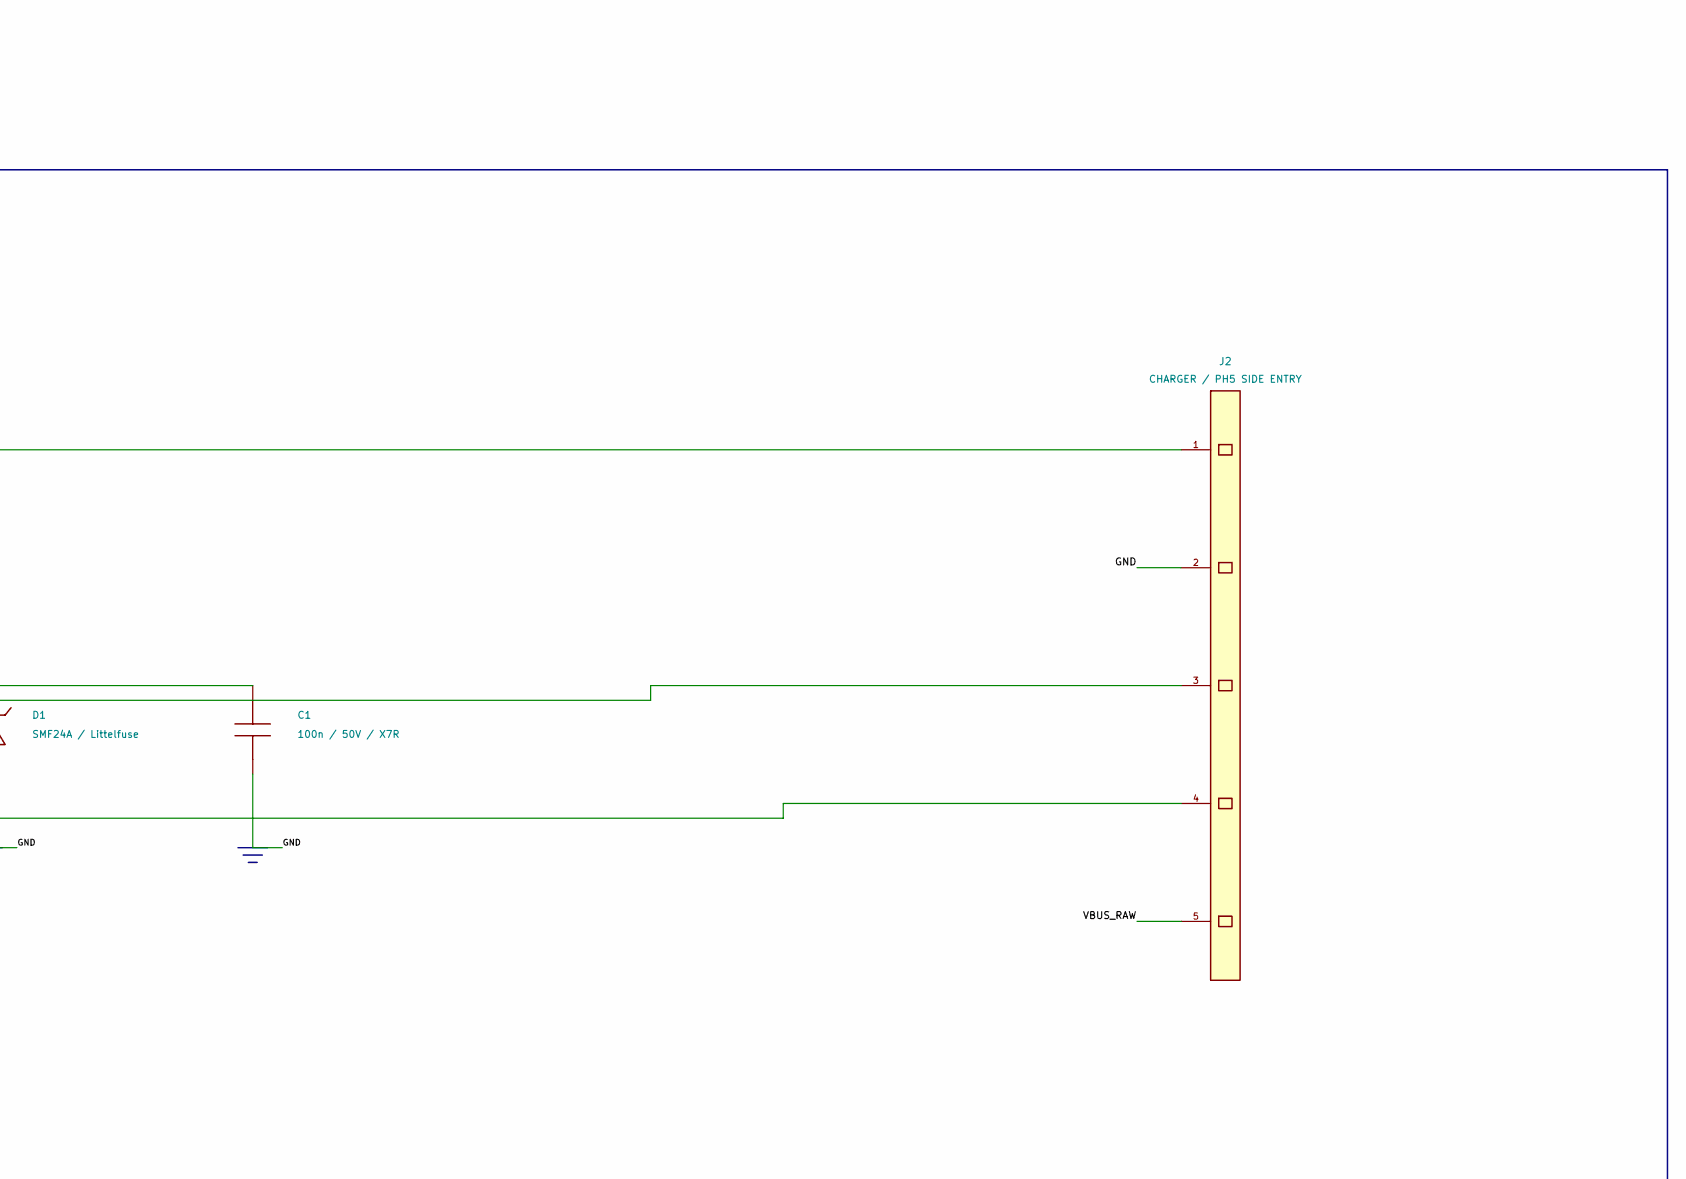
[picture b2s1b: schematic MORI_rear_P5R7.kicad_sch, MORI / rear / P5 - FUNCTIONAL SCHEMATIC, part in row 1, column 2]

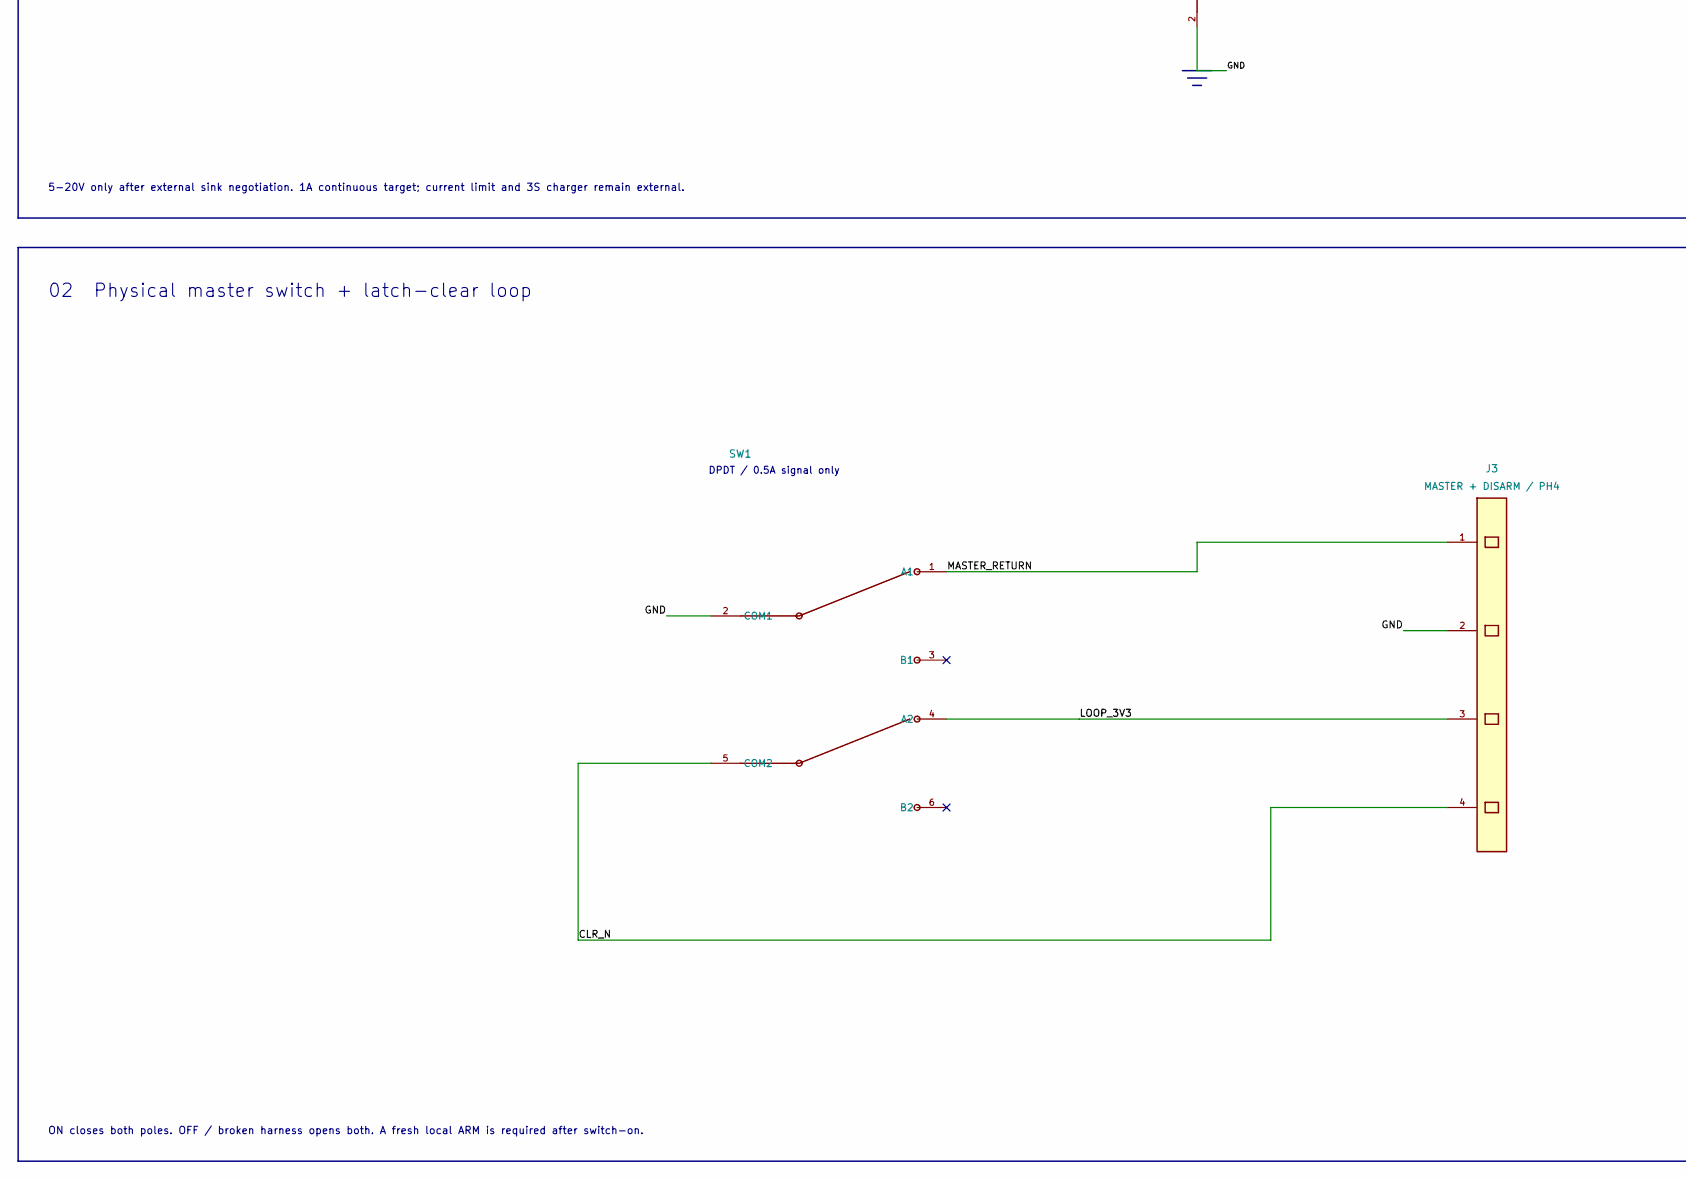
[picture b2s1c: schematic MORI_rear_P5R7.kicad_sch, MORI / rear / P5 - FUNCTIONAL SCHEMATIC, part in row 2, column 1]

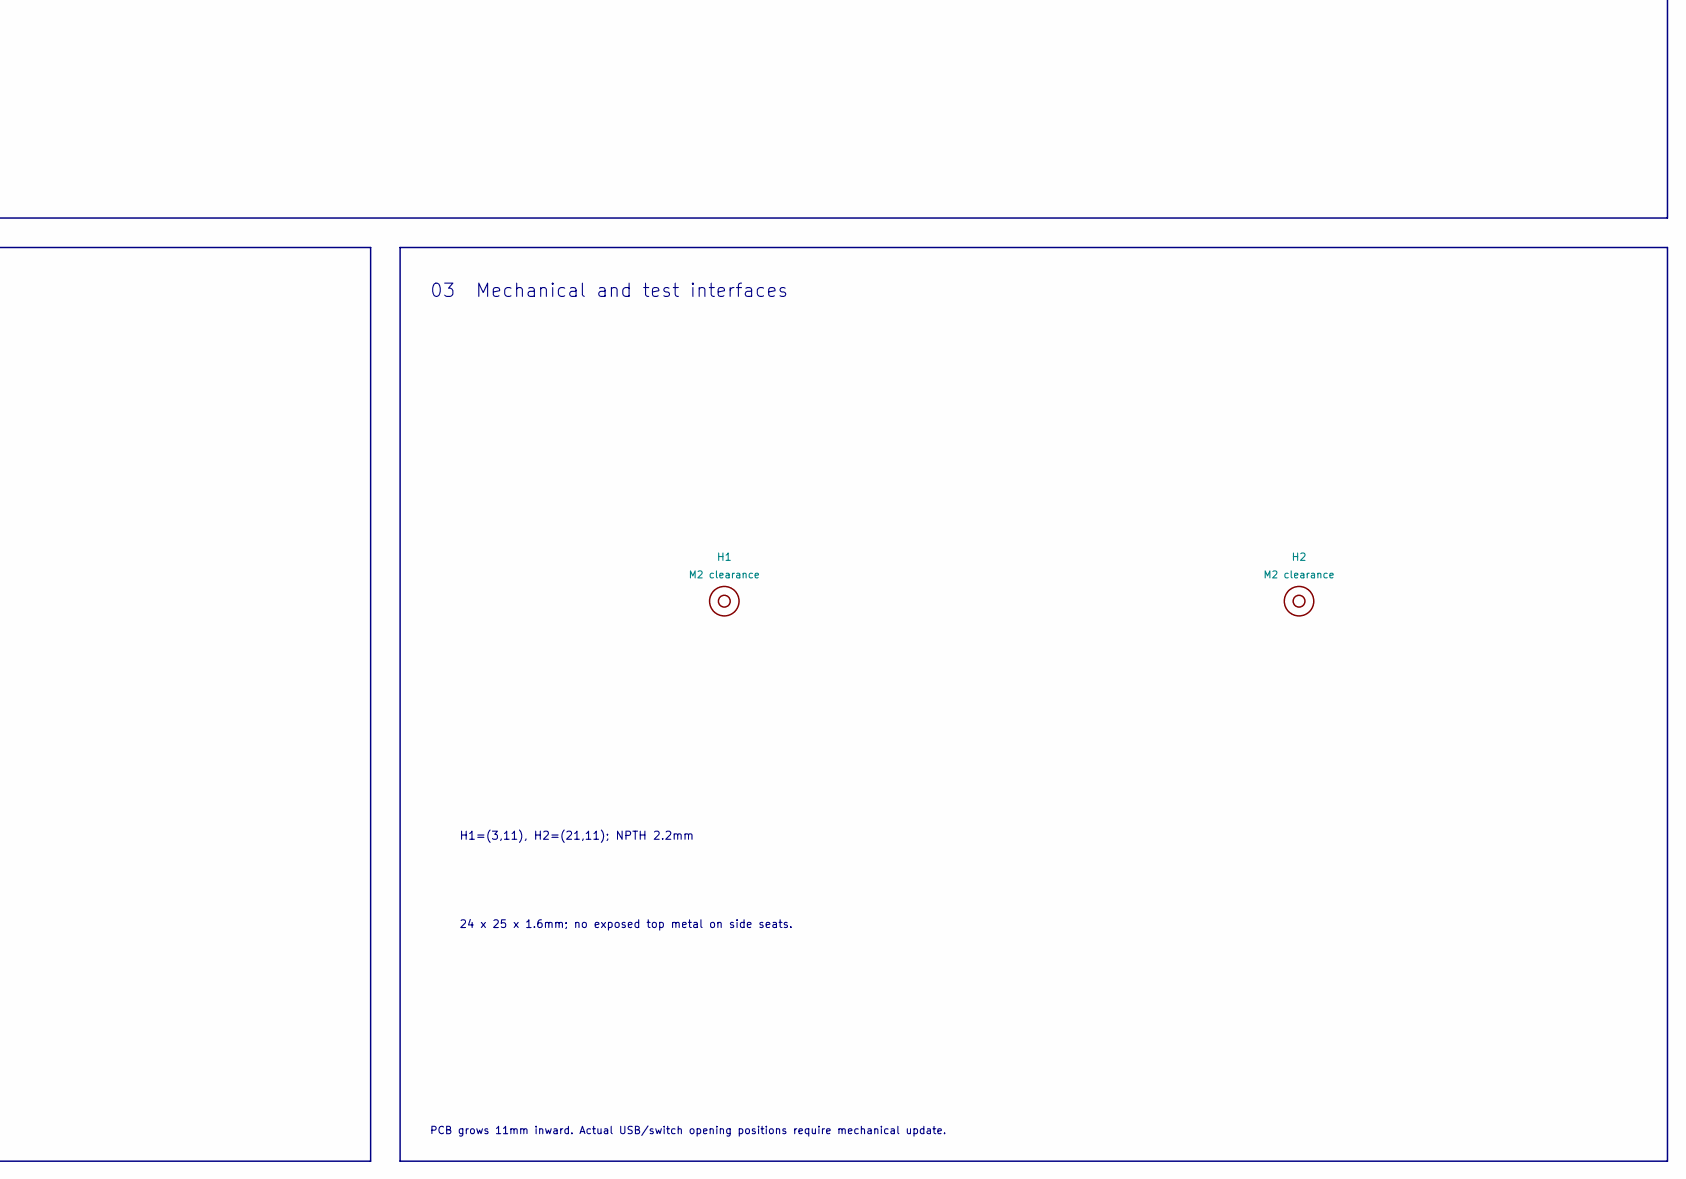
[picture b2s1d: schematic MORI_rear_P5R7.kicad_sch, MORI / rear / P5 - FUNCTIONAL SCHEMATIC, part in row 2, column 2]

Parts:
C1: 100n / 50V / X7R; C_0603_1608Metric
D1: SMF24A / Littelfuse; D_SOD-123F__P5_D1
D2: PESD5V0L1BA,115; D_SOD-323__P5_D2
D3: PESD5V0L1BA,115; D_SOD-323__P5_D3
F1: 045101.5MRL / 1.5A; Littelfuse_451_6.1x2.69_P4__P3R1_F1
H1, H2: M2 clearance; MountingHole_2.2mm_M2
J2: CHARGER / PH5 SIDE ENTRY; JST_PH_S5B-PH-K_1x05_P2.00mm_Horizontal__P4_ANNULUS__P5_J2
J3: MASTER + DISARM / PH4; JST_PH_B4B-PH-K_1x04_P2.00mm_Vertical__P4_ANNULUS__P3R1_J3
SW1: SOFNG MS-202V-G3; SOFNG_MS202V_G3_P4__P5_SW1
USB1: HRO TYPE-C-31-M-12 / charge only; USB_C_Receptacle_HRO_TYPE-C-31-M-12__P4_ANNULUS__P5_USB1

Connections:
/CC1: D2.1, J2.3, USB1.A5 (CC1)
/CC2: D3.1, J2.4, USB1.B5 (CC2)
/CLR_N: J3.4, SW1.5 (COM2)
/GND: C1.2, D1.2, D2.2, D3.2, J2.2, J3.2, SW1.2 (COM1), USB1.A1, USB1.A12, USB1.B1, USB1.B12, USB1.SH
/LOOP_3V3: J3.3, SW1.4 (A2)
/MASTER_RETURN: J3.1, SW1.1 (A1)
/VBUS_FUSED: C1.1, D1.1, F1.2, J2.1
/VBUS_RAW: F1.1, J2.5, USB1.A4, USB1.A9, USB1.B4, USB1.B9

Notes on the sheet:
MORI / REAR TYPE-C + POWER SWITCH / P4
PROTOTYPE / NOT_TESTED. No PD negotiation or battery CC/CV charging on this interface board.
01 USB-C charge inlet / fuse / CC pass-through
5-20V only after external sink negotiation. 1A continuous target; current limit and 3S charger remain external.
USB-C / HRO 31-M-12
1.5A / 125VDC
CC1 ESD
CC2 ESD
02 Physical master switch + latch-clear loop
ON closes both poles. OFF / broken harness opens both. A fresh local ARM is required after switch-on.
DPDT / 0.5A signal only
03 Mechanical and test interfaces
PCB grows 11mm inward. Actual USB/switch opening positions require mechanical update.
H1=(3,11), H2=(21,11); NPTH 2.2mm
24 x 25 x 1.6mm; no exposed top metal on side seats.

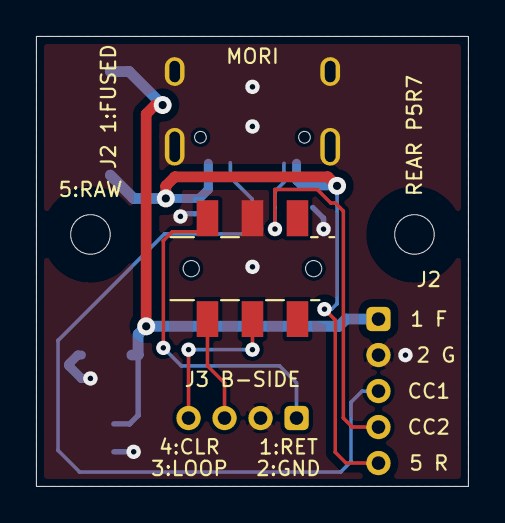
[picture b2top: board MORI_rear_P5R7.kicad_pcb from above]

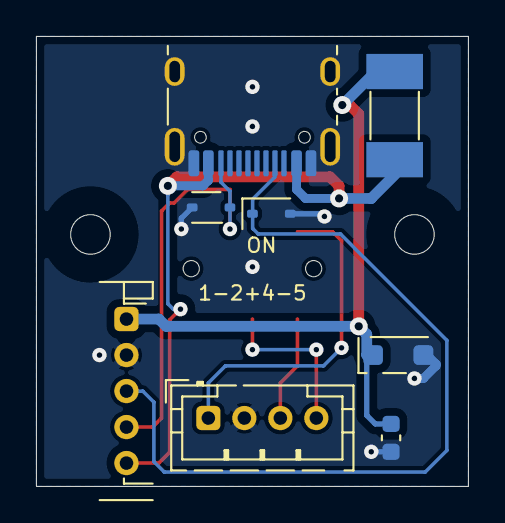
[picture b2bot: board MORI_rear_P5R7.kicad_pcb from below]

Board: 2 copper layers, 24.0 x 25.0 mm, 11 parts (8 on the bottom side), 8 nets.
